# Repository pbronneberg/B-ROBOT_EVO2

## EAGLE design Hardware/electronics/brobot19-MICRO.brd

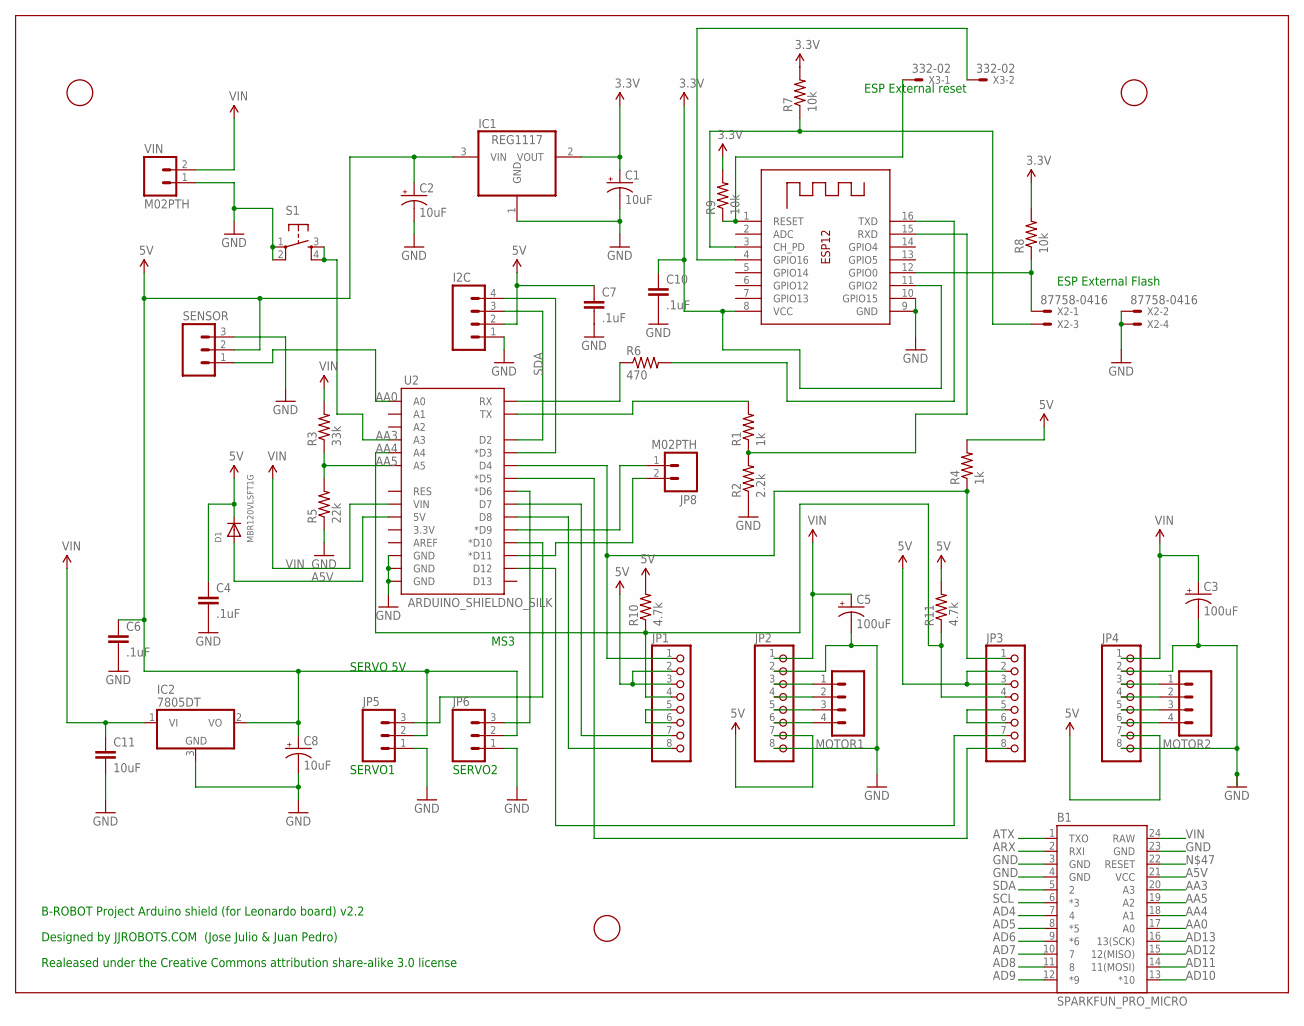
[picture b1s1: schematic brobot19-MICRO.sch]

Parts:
B1: SPARKFUN_PRO_MICRO
C1, C2, C8: 10uF; EIA3216
C3, C5: 100uF; PANASONIC_D
C4, C6, C7, C10: .1uF; 0402-CAP
C11: 10uF; 1206
D1: MBR120VLSFT1G; SOD-123
I2C: M04PTH; 1X04
IC1: REG1117; SOT223
IC2: 7805DT; TO252
JP1, JP2, JP3, JP4: PINHD-1X8; 1X08
JP5, JP6: M03PTH; 1X03
JP8: M02PTH; 1X02
MOTOR1, MOTOR2: M04PTH; 1X04
R1, R4: 1k; 0805
R2: 2.2k; 0805
R3: 33k; 0805
R5: 22k; 0805
R6: 470; 0805
R7, R8, R9: 10k; 0805
R10, R11: 4.7k; 0805
S1: TAC_SWITCHSMD; TACTILE-SWITCH-SMD
SENSOR: M03PTH; 1X03
U2: ARDUINO_SHIELDNO_SILK; DUEMILANOVE_VIAS
U$1, U$2, U$3: FIDUCIAL; FIDUCIAL_1MM
VIN: M02PTH; 1X02
X1: ESP-12
X2: 87758-0416
X3: 332-02

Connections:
3.3V: C1.A (+), C10.1, IC1.2 (VOUT), R7.2, R8.2, R9.2, X1.8 (VCC), X1.11 (GPIO2)
5V: C2.A (+), C4.1, C6.1, C7.1, C8.A (+), D1.C, I2C.2, IC1.3 (VIN), IC2.2 (VO), JP1.2, JP1.3, JP2.7, JP3.2, JP3.3, JP4.7, JP5.2, JP6.2, R4.2, R10.2, R11.2, SENSOR.2
A5V: B1.21 (VCC), D1.A, U2.5V
AA0: B1.17 (A0), SENSOR.1, U2.A0
AA3: B1.20 (A3), S1.3, S1.4, U2.A3
AA4: B1.18 (A1), JP1.4, JP3.4, R10.1, R11.1, U2.A4
AA5: B1.19 (A2), R3.1, R5.2, U2.A5
AD4: B1.7 (4), JP1.1, JP3.1, R4.1, U2.D4
AD5: B1.8 (*5), JP3.8, U2.D5 (*D5)
AD6: B1.9 (*6), JP6.3, U2.D6 (*D6)
AD7: B1.10 (7), JP1.7, U2.D7
AD8: B1.11 (8), JP1.8, U2.D8
AD9: B1.12 (*9), JP8.1, U2.D9 (*D9)
AD10: B1.13 (*10), JP5.3, U2.D10 (*D10)
AD11: B1.14 (11(MOSI)), JP8.2, U2.D11 (*D11)
AD12: B1.15 (12(MISO)), JP3.7, U2.D12
AD13: B1.16 (13(SCK))
ARX: B1.2 (RXI), R6.1, U2.RX
ATX: B1.1 (TXO), R1.2, U2.TX
GND: B1.3 (GND), B1.4 (GND), B1.23 (GND), C1.C (-), C2.C (-), C3.-, C4.2, C5.-, C6.2, C7.2, C8.C (-), C10.2, C11.2, I2C.1, IC1.1 (GND), IC2.3 (GND), JP2.2, JP2.8, JP4.2, JP4.8, JP5.1, JP6.1, R2.1, R5.1, S1.1, S1.2, SENSOR.3, U2.GND@0 (GND), U2.GND@1 (GND), U2.GND@2 (GND), VIN.1, X1.9 (GND), X1.10 (GPIO15), X2.2, X2.4
unnamed: JP2.3, MOTOR1.1
unnamed: JP2.4, MOTOR1.2
unnamed: R6.2, X1.16 (TXD)
unnamed: R1.1, R2.2, X1.15 (RXD)
unnamed: JP2.5, MOTOR1.3
unnamed: JP2.6, MOTOR1.4
unnamed: JP4.3, MOTOR2.1
unnamed: JP4.4, MOTOR2.2
unnamed: JP4.5, MOTOR2.3
unnamed: JP1.5, JP1.6
unnamed: JP3.5, JP3.6
unnamed: JP4.6, MOTOR2.4
unnamed: R7.1, X1.3 (CH_PD), X2.3
unnamed: R8.1, X1.12 (GPIO0), X2.1
unnamed: R9.1, X1.1 (RESET), X3.1
unnamed: X1.4 (GPIO16), X3.2
SCL: B1.6 (*3), I2C.4, U2.D3 (*D3)
SDA: B1.5 (2), I2C.3, U2.D2
VIN: B1.24 (RAW), C3.+, C5.+, C11.1, IC2.1 (VI), JP2.1, JP4.1, R3.2, U2.VIN, VIN.2

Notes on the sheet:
SERVO 5V
B-ROBOT Project Arduino shield (for Leonardo board) v2.2
Designed by JJROBOTS.COM (Jose Julio & Juan Pedro)
Realeased under the Creative Commons attribution share-alike 3.0 license
ESP External reset
ESP External Flash
SERVO1
SERVO2
MS3

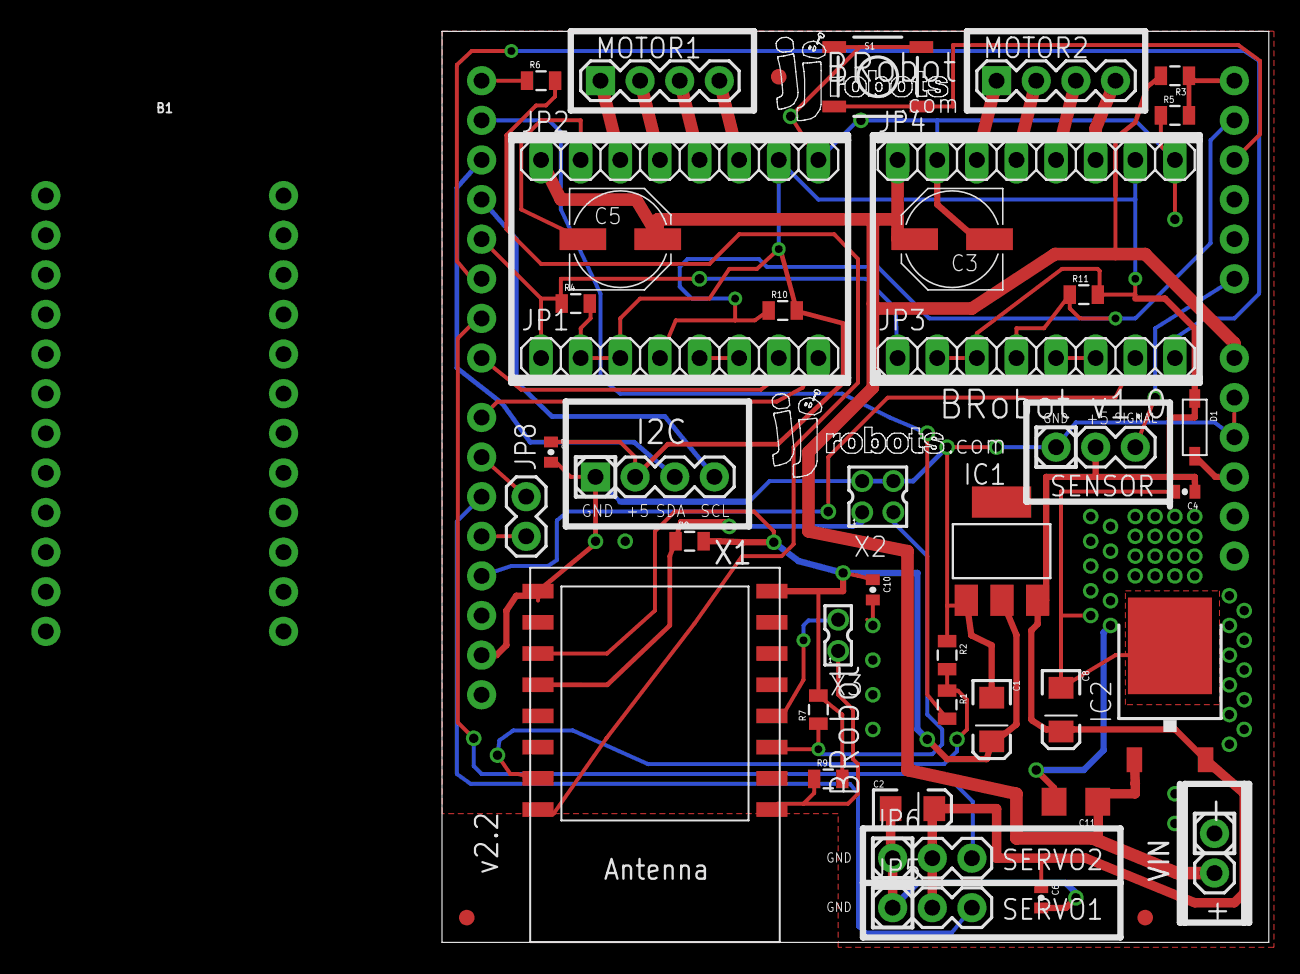
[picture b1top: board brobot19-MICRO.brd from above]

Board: 2 copper layers, 53.0 x 58.4 mm, 45 parts (0 on the bottom side), 38 nets.

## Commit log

2018-05-05 added board file from forum. and first version of micro version

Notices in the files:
parts and their libraries:
SparkFun-Boards: Licensing: Creative Commons ShareAlike 4.0 International - https://creativecommons.org/licenses/by-sa/4.0
